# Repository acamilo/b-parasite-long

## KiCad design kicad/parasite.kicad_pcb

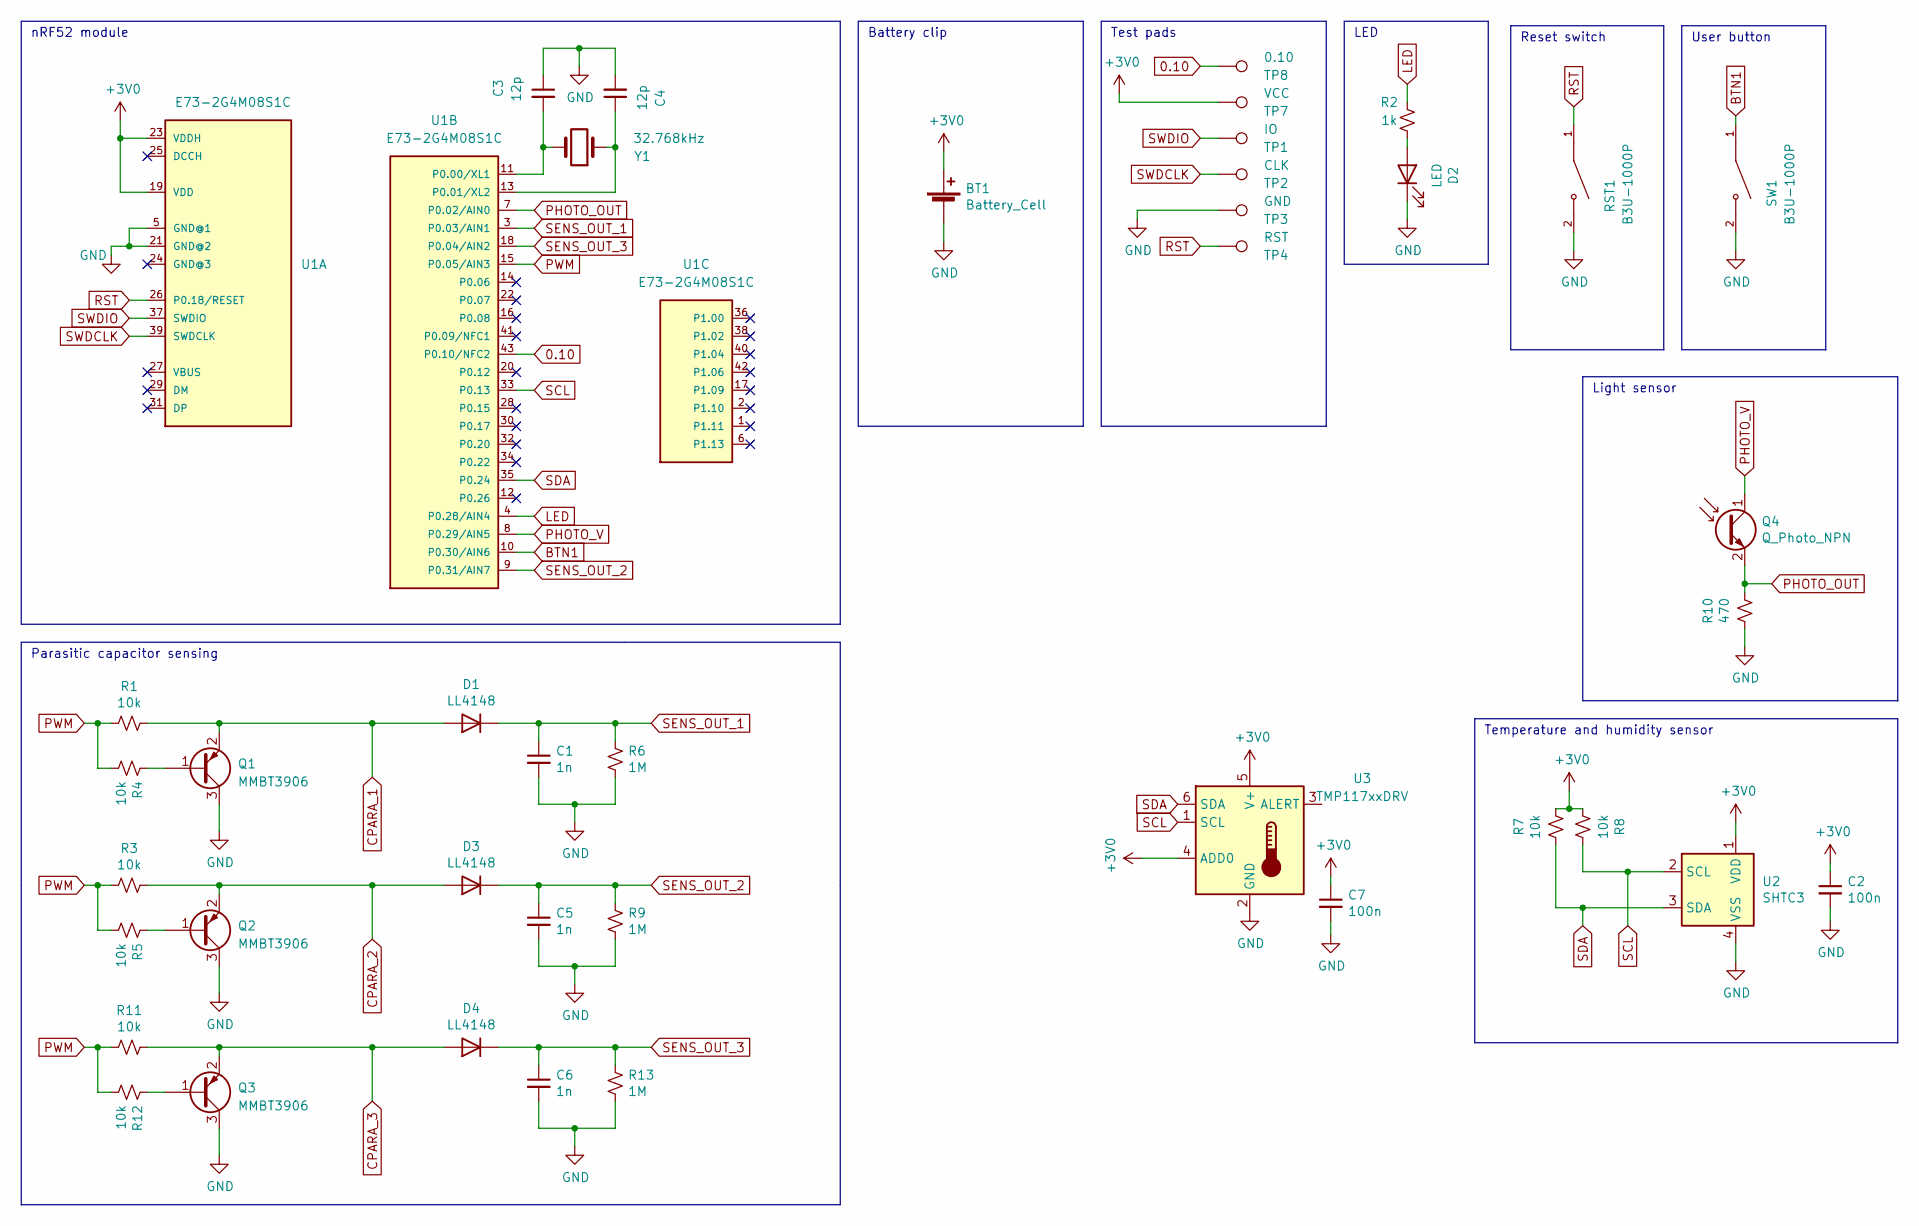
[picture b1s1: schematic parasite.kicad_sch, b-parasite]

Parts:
BT1: Battery_Cell; BatteryHolder_Keystone_3002_1x2032
C1, C5, C6: 1n; C_0402_1005Metric; LCSC C1523
C2, C7: 100n; C_0402_1005Metric; LCSC C1525
C3, C4: 12p; C_0402_1005Metric; LCSC C1547
D1, D3, D4: LL4148; D_MiniMELF; LCSC C9808
D2: LED; LED_0603_1608Metric; LCSC C2286
Q1, Q2, Q3: MMBT3906; SOT-23; LCSC C2910191
Q4: Q_Photo_NPN; TR8; LCSC C146233
R1, R3, R4, R5, R7, R8, R11, R12: 10k; R_0402_1005Metric; LCSC C25744
R2: 1k; R_0402_1005Metric; LCSC C11702
R6, R9, R13: 1M; R_0402_1005Metric; LCSC C26083
R10: 470; R_0402_1005Metric; LCSC C25117
RST1: B3U-1000P; SW_B3U-1000P; LCSC C231329
SW1: B3U-1000P; SW_B3U-1000P; LCSC C231329
TP1: IO; TestPoint_Pad_D1.0mm
TP2: CLK; TestPoint_Pad_D1.0mm
TP3: GND; TestPoint_Pad_D1.0mm
TP4: RST; TestPoint_Pad_D1.0mm
TP7: VCC; TestPoint_Pad_D1.0mm
TP8: 0.10; TestPoint_Pad_D1.0mm
U1: E73-2G4M08S1C
U2: SHTC3; Sensirion_DFN-4-1EP_2x2mm_P1mm_EP0.7x1.6mm; LCSC C194656
U3: TMP117xxDRV; WSON-6-1EP_2x2mm_P0.65mm_EP1x1.6mm; LCSC C2803242
Y1: 32.768kHz; Crystal_SMD_3215-2Pin_3.2x1.5mm; LCSC C32346

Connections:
0.10: TP8.1, U1.43 (P0.10/NFC2)
+3V0: BT1.1 (+), C2.1, C7.1, R7.2, R8.1, TP7.1, U1.19 (VDD), U1.23 (VDDH), U2.1 (VDD), U3.4 (ADD0), U3.5 (V+)
BTN1: SW1.1, U1.10 (P0.30/AIN6)
CPARA_1: D1.2 (A), Q1.2 (E), R1.2
CPARA_2: D3.2 (A), Q2.2 (E), R3.2
CPARA_3: D4.2 (A), Q3.2 (E), R11.2
GND: BT1.2 (-), C1.2, C2.2, C3.1, C4.2, C5.2, C6.2, C7.2, D2.1 (K), Q1.3 (C), Q2.3 (C), Q3.3 (C), R6.2, R9.2, R10.1, R13.2, RST1.2, SW1.2, TP3.1, U1.5 (GND@1), U1.21 (GND@2), U2.4 (VSS), U3.2 (GND)
LED: R2.2, U1.4 (P0.28/AIN4)
unnamed: D2.2 (A), R2.1
unnamed: Q1.1 (B), R4.1
unnamed: Q2.1 (B), R5.1
unnamed: Q3.1 (B), R12.1
unnamed: C3.2, U1.11 (P0.00/XL1), Y1.2
unnamed: C4.1, U1.13 (P0.01/XL2), Y1.1
PHOTO_OUT: Q4.2 (E), R10.2, U1.7 (P0.02/AIN0)
PHOTO_V: Q4.1 (C), U1.8 (P0.29/AIN5)
PWM: R1.1, R3.1, R4.2, R5.2, R11.1, R12.2, U1.15 (P0.05/AIN3)
RST: RST1.1, TP4.1, U1.26 (P0.18/RESET)
SCL: R8.2, U1.33 (P0.13), U2.2 (SCL), U3.1 (SCL)
SDA: R7.1, U1.35 (P0.24), U2.3 (SDA), U3.6 (SDA)
SENS_OUT_1: C1.1, D1.1 (K), R6.1, U1.3 (P0.03/AIN1)
SENS_OUT_2: C5.1, D3.1 (K), R9.1, U1.9 (P0.31/AIN7)
SENS_OUT_3: C6.1, D4.1 (K), R13.1, U1.18 (P0.04/AIN2)
SWDCLK: TP2.1, U1.39 (SWDCLK)
SWDIO: TP1.1, U1.37 (SWDIO)

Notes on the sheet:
Temperature and humidity sensor
LED
nRF52 module
Parasitic capacitor sensing
Test pads
Light sensor
Reset switch
User button
Battery clip

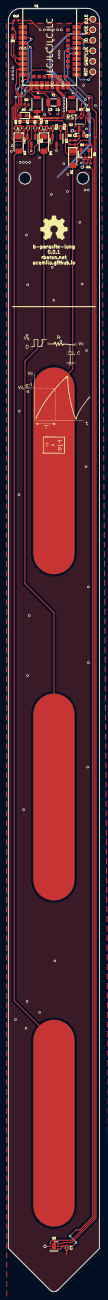
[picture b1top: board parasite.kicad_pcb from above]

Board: 2 copper layers, 22.0 x 309.8 mm, 41 parts (1 on the bottom side), 25 nets.

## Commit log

2024-01-27 Created a new board definition for long variant
2024-01-28 Add code for 2 additional sensors
2024-01-28 wrangled device tree to add 2 more ADC channels
2024-01-28 Update Schematic to add 2 more sense points
2024-01-28 updated PCB with 3 zones and soil temp sensor
2024-01-28 added lcsc part numbers and a temp sensor
2024-02-29 Update encoding.c
    Fix error in array index
2024-02-29 Add TMP117 temp sensor
2024-02-29 Fixed i2c address pin issue
    Connected pin to 3v to program 0x49 address
2024-03-01 Updated BThome report to fit into advertising payload.
